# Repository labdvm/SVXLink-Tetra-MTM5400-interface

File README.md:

# SVXLink-Tetra-MTM5400-interface
SVXLink-Tetra dedicated interface for MTM5400 and USB audio card.
This is dedicated inteface for Motorola MTM5400 and USB Audio card CM108 and others.
V1.5.
Z32IT

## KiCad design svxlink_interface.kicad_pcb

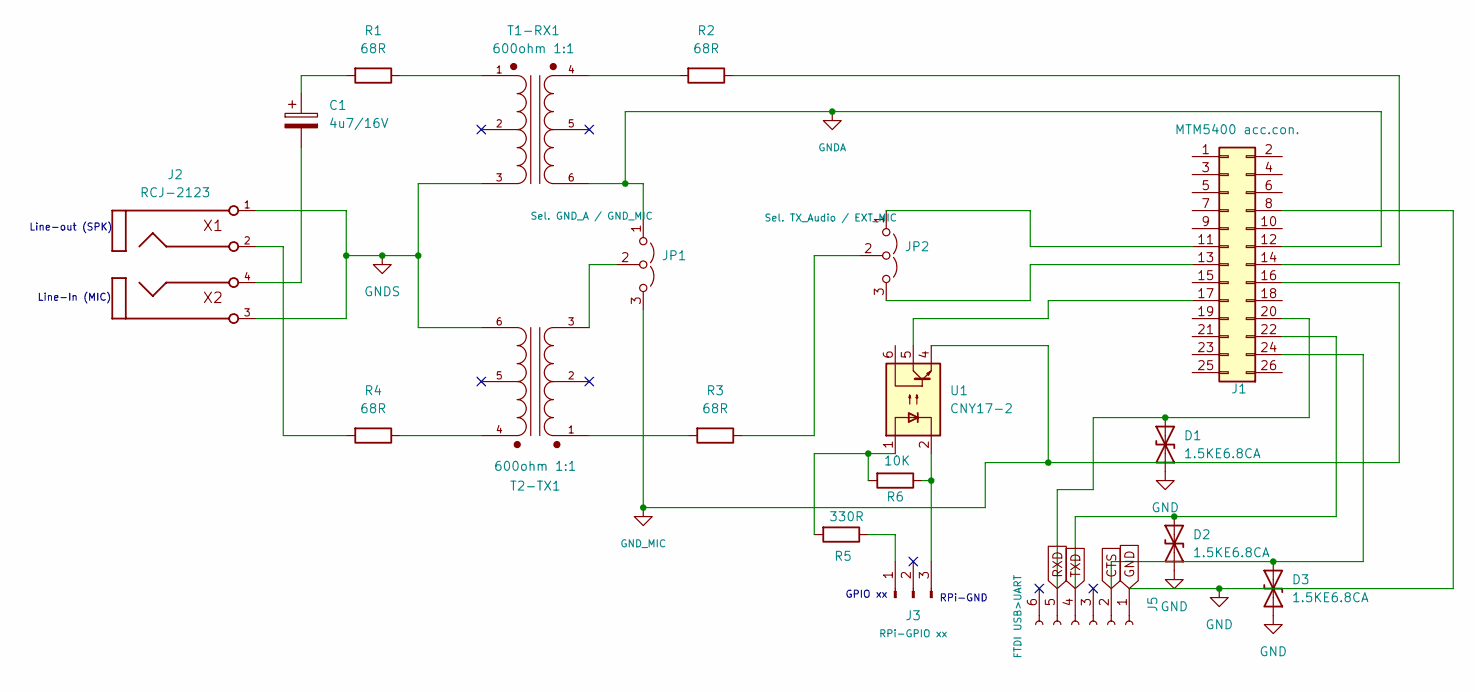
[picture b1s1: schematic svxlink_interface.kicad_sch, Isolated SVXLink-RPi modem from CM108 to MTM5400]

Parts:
C1: 4u7/16V; CP_Radial_D4.0mm_P2.00mm
D1, D2, D3: 1.5KE6.8CA; D_DO-201AE_P15.24mm_Horizontal
J1: MTM5400 acc.con.; MTM5400_1
J2: RCJ-2123; RCJ-2121
J3: RPi-GPIO xx; PinHeader_1x03_P2.54mm_Vertical
J5: FTDI USB>UART; PinSocket_1x06_P2.54mm_Horizontal
JP1: Sel. GND_A / GND_MIC; PinHeader_1x03_P2.54mm_Vertical
JP2: Sel. TX_Audio / EXT_MIC; PinHeader_1x03_P2.54mm_Vertical
R1, R2, R3, R4: 68R; R_Axial_DIN0207_L6.3mm_D2.5mm_P10.16mm_Horizontal
R5: 330R; R_Axial_DIN0207_L6.3mm_D2.5mm_P10.16mm_Horizontal
R6: 10K; R_Axial_DIN0207_L6.3mm_D2.5mm_P10.16mm_Horizontal
T1-RX1, T2-TX1: 600ohm 1:1; XFMR_TY-145P; PARTREV 2016
U1: CNY17-2; DIP-6_W7.62mm_Socket

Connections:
CTS: D3.2 (A2), J1.24 (CTS), J5.2
GND: D1.1 (A1), D2.1 (A1), D3.1 (A1), J1.8 (GND), J5.1
GNDA: J1.12 (GND_A), JP1.1 (A), T1-RX1.6
GNDS: J2.1, J2.3, T1-RX1.3, T2-TX1.6
GND_MIC: J1.16 (GND_MIC), JP1.3 (B), U1.4
unnamed: C1.1, R1.2
unnamed: C1.2, J2.4
unnamed: J1.13 (EXT_MIC), JP2.3 (B)
unnamed: J1.17 (PTT), U1.5
unnamed: J1.14 (RX_Audio), R2.1
unnamed: J1.11 (TX_Audio), JP2.1 (A)
unnamed: J2.2, R4.2
unnamed: J3.1, R5.1
unnamed: J3.3, R6.1, U1.2
unnamed: JP1.2 (C), T2-TX1.3
unnamed: JP2.2 (C), R3.1
unnamed: R1.1, T1-RX1.1
unnamed: R2.2, T1-RX1.4
unnamed: R3.2, T2-TX1.1
unnamed: R4.1, T2-TX1.4
unnamed: R5.2, R6.2, U1.1
RXD: D1.2 (A2), J1.20 (TXD), J5.5
TXD: D2.2 (A2), J1.22 (RXD), J5.4

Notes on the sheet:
Line-In (MIC)
Line-out (SPK)
RPi-GND
GPIO xx

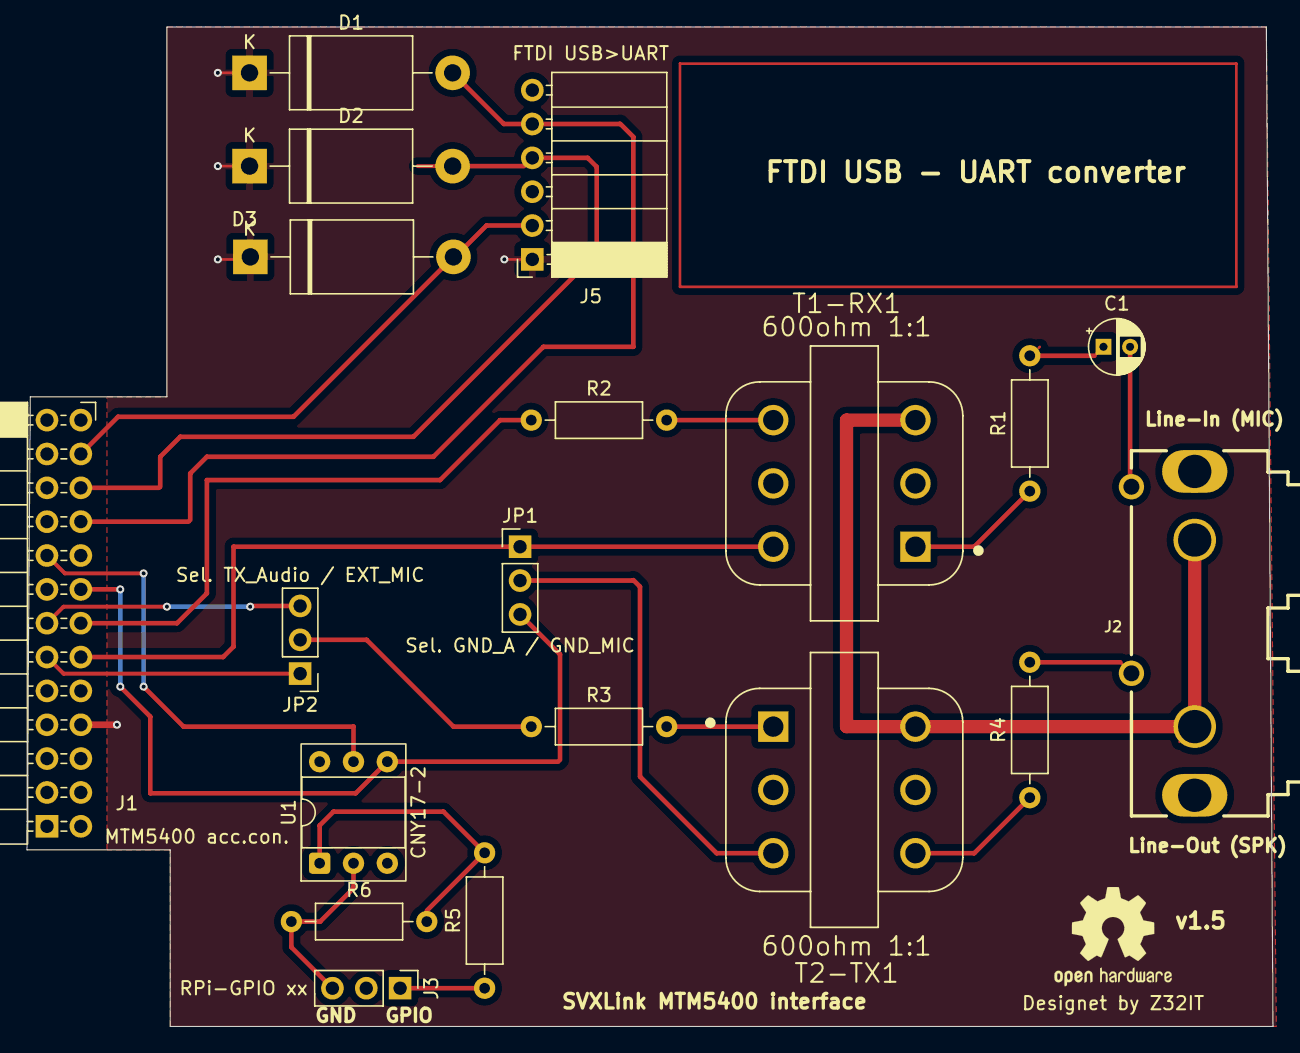
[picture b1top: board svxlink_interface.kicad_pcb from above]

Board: 2 copper layers, 93.5 x 75.0 mm, 19 parts (0 on the bottom side), 23 nets.

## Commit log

2025-12-31 Add description for MTM5400 and CM108 interface
2026-01-01 Update README with version and author details
    Added version number and author information.
